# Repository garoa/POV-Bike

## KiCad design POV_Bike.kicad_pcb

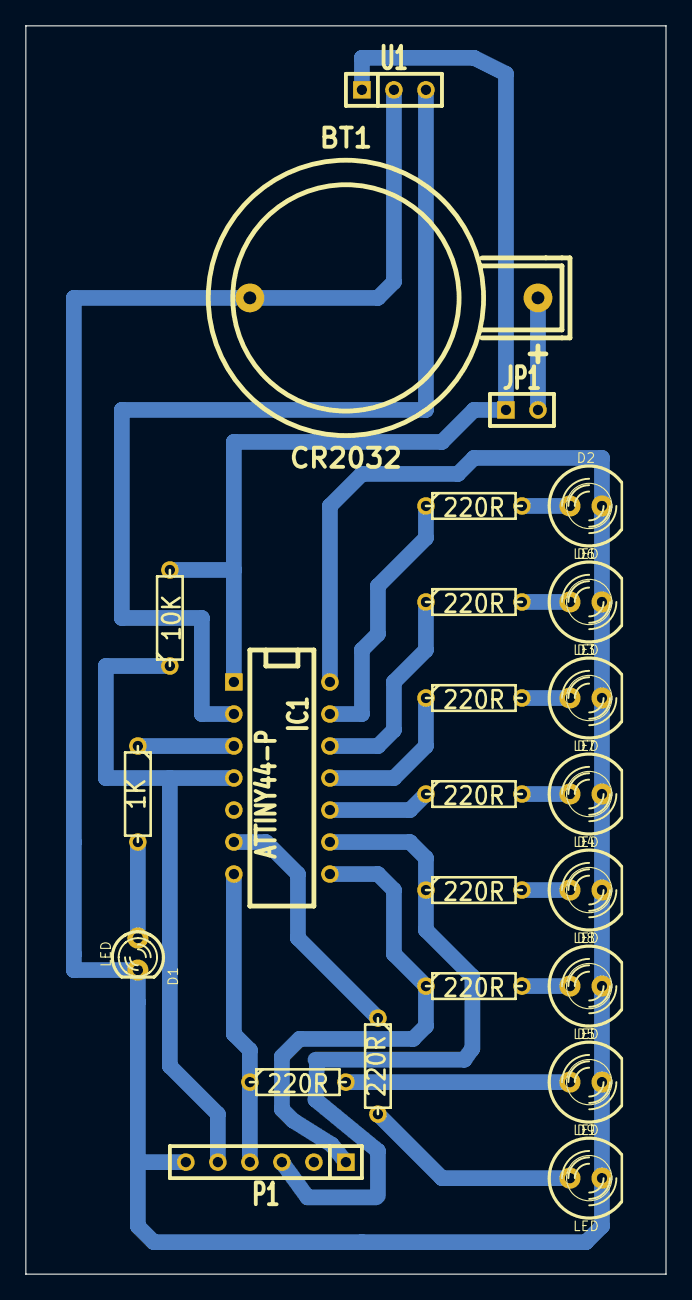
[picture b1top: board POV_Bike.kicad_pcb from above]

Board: 2 copper layers, 50.8 x 99.1 mm, 24 parts (0 on the bottom side), 23 nets.

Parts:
BT1: CR2032; CR2032H
D1: LED; LED-3MM
D2, D3, D4, D5, D6, D7, D8, D9: LED; LED-5MM
IC1: ATTINY44-P; DIP-14__300
JP1: JUMPER; SIL-2
P1: CONN_6; SIL-6
R1: 1K; R3
R2: 10K; R3
R3, R4, R5, R6, R7, R8, R9, R10: 220R; R3
U1: A1120; SIL-3

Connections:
+BATT: IC1.1, JP1.1, R2.2, U1.1
GND: BT1.2, D1.2, D2.2, D3.2, D4.2, D5.2, D6.2, D7.2, D8.2, D9.2, IC1.14, P1.6, U1.2
unnamed: IC1.4, P1.5, R2.1
unnamed: IC1.2, U1.3
unnamed: BT1.1, JP1.2
unnamed: IC1.3, R1.1
unnamed: D1.1, R1.2
unnamed: D7.1, R8.2
unnamed: D8.1, R9.2
unnamed: D6.1, R7.2
unnamed: D9.1, R10.2
unnamed: D3.1, R4.2
unnamed: D4.1, R5.2
unnamed: IC1.11, R4.1
unnamed: IC1.6, R10.1
unnamed: IC1.7, P1.4, R6.1
unnamed: IC1.8, P1.1, R9.1
unnamed: IC1.9, P1.3, R5.1
unnamed: IC1.10, R8.1
unnamed: D5.1, R6.2
unnamed: IC1.13, R3.1
unnamed: D2.1, R3.2
unnamed: IC1.12, R7.1

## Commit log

2015-02-03 POV Bike - Versao inicial
2015-02-03 Adicao do firmware
2015-02-06 Melhorias no layout da placa
